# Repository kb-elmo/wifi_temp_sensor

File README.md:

# Wifi temp sensor

[![CC BY-NC-SA 4.0][cc-by-nc-sa-shield]][cc-by-nc-sa]

### ESP-12F/DHT22 powered temperature/humidity sensor module

This work is licensed under a
[Creative Commons Attribution-NonCommercial-ShareAlike 4.0 International License][cc-by-nc-sa].

[![CC BY-NC-SA 4.0][cc-by-nc-sa-image]][cc-by-nc-sa]

[cc-by-nc-sa]: http://creativecommons.org/licenses/by-nc-sa/4.0/
[cc-by-nc-sa-image]: https://licensebuttons.net/l/by-nc-sa/4.0/88x31.png
[cc-by-nc-sa-shield]: https://img.shields.io/badge/License-CC%20BY--NC--SA%204.0-lightgrey.svg

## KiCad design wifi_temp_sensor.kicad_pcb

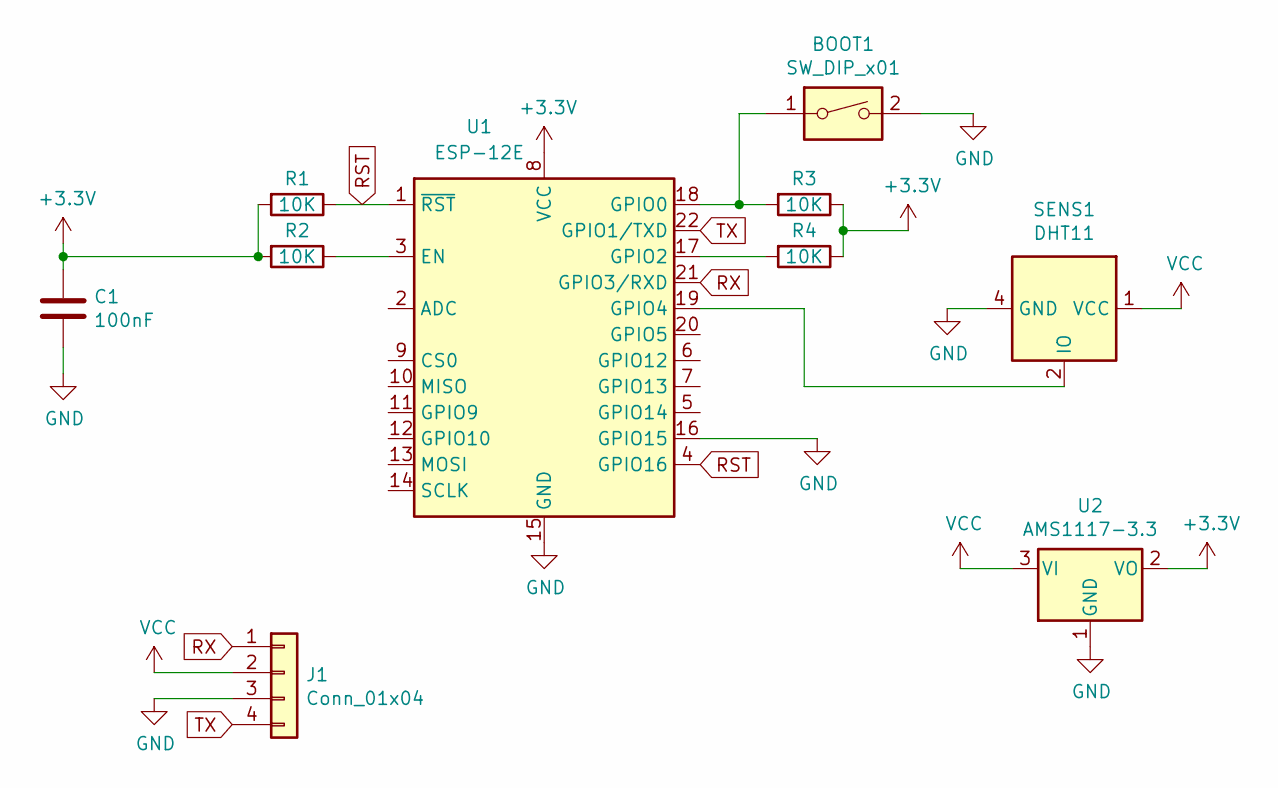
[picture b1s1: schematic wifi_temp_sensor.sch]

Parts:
BOOT1: SW_DIP_x01; SW_DIP_SPSTx01_Slide_9.78x4.72mm_W7.62mm_P2.54mm
C1: 100nF; C_Disc_D5.0mm_W2.5mm_P5.00mm
J1: Conn_01x04; PinHeader_1x04_P2.54mm_Horizontal
R1, R2, R3, R4: 10K; R_Axial_DIN0207_L6.3mm_D2.5mm_P10.16mm_Horizontal
SENS1: DHT11; DHT22
U1: ESP-12E; ESP-12F
U2: AMS1117-3.3; PinSocket_1x03_P2.54mm_Vertical

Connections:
+3V3: C1.1, R1.2, R2.2, R3.1, R4.1, U1.8 (VCC), U2.2 (VO)
GND: BOOT1.2, C1.2, J1.3, SENS1.4 (GND), U1.15 (GND), U1.16 (GPIO15), U2.1 (GND); also elsewhere on the board
unnamed 2: BOOT1.1, R3.2, U1.18 (GPIO0); also elsewhere on the board
unnamed: R2.1, U1.3 (EN)
unnamed: R4.2, U1.17 (GPIO2)
unnamed: SENS1.2 (IO), U1.19 (GPIO4)
RST: R1.1, U1.1 (~RST), U1.4 (GPIO16)
RX: J1.1, U1.21 (GPIO3/RXD)
TX: J1.4, U1.22 (GPIO1/TXD)
VCC: J1.2, SENS1.1 (VCC), U2.3 (VI)

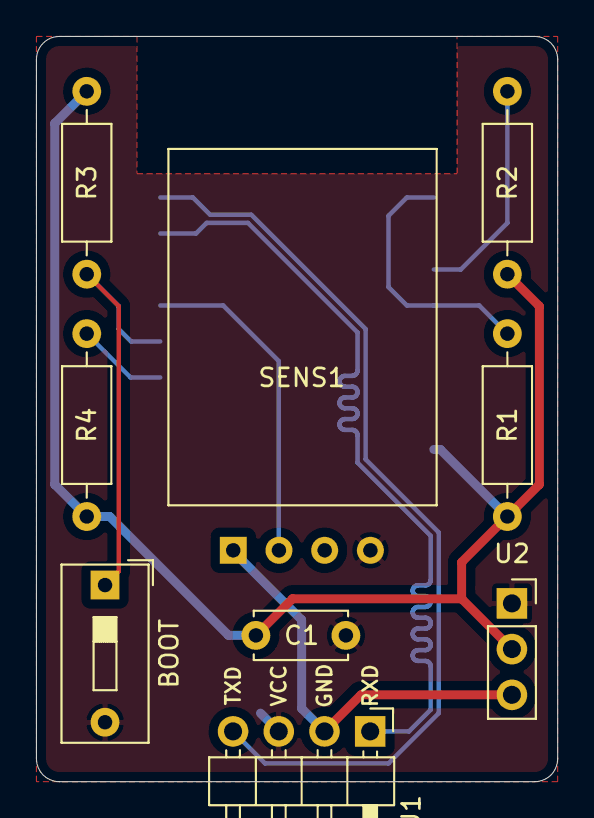
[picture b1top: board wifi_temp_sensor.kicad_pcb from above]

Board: 2 copper layers, 29.0 x 41.4 mm, 10 parts (1 on the bottom side), 10 nets.

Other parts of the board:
BOOT: SW_DIP_x01; SW_DIP_SPSTx01_Slide_9.78x4.72mm_W7.62mm_P2.54mm

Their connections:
GND: BOOT.2; also elsewhere on the board
unnamed 2: BOOT.1; also elsewhere on the board

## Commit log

2020-10-29 update files
